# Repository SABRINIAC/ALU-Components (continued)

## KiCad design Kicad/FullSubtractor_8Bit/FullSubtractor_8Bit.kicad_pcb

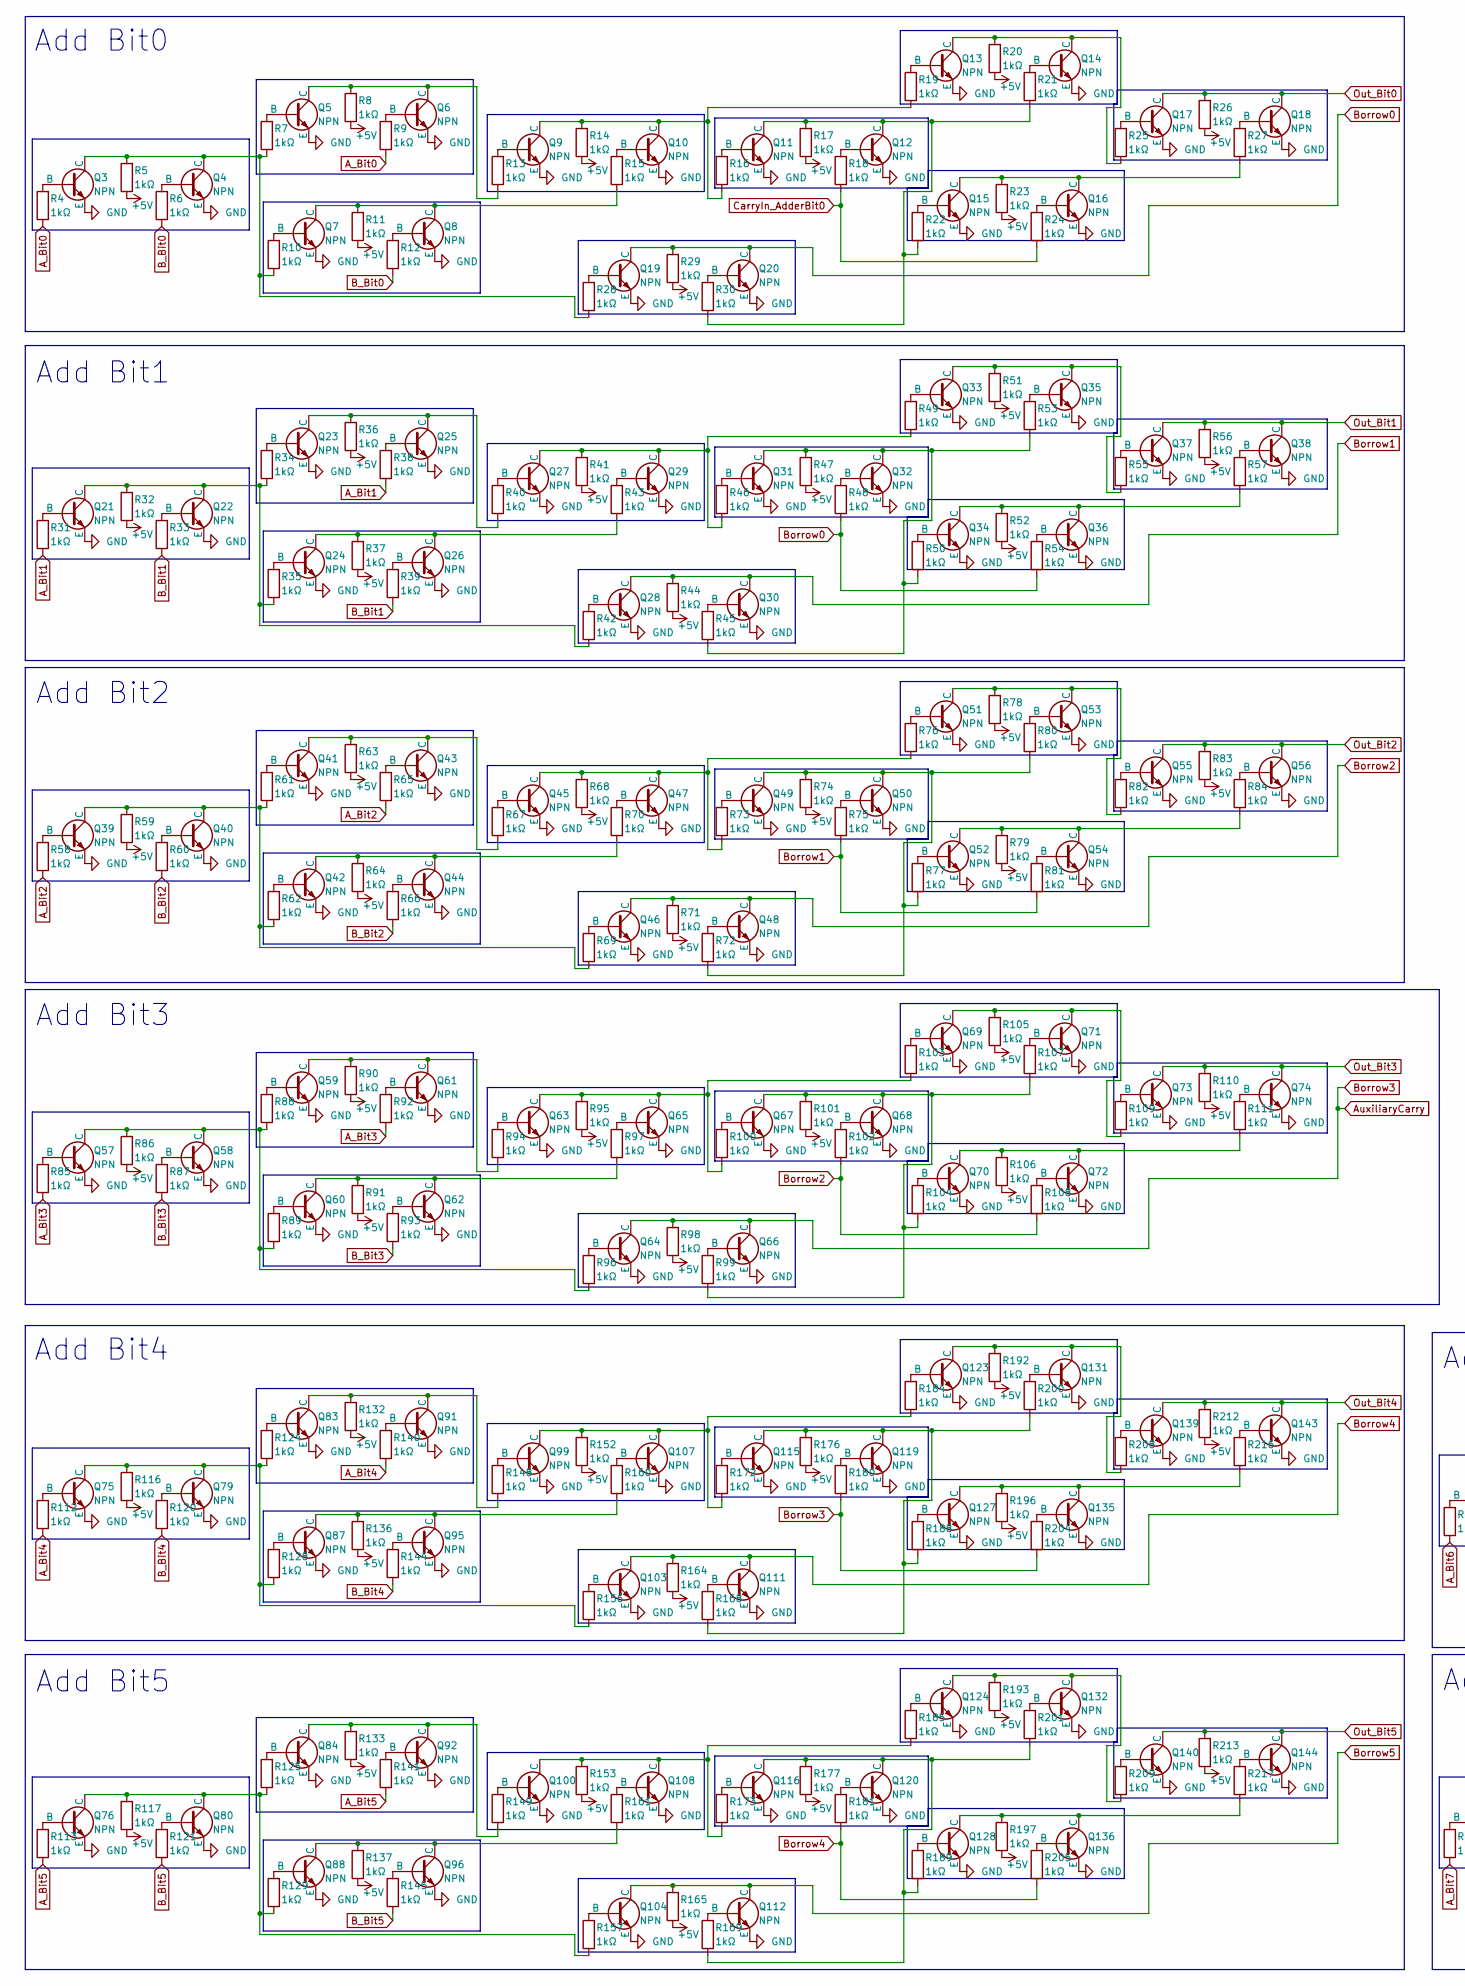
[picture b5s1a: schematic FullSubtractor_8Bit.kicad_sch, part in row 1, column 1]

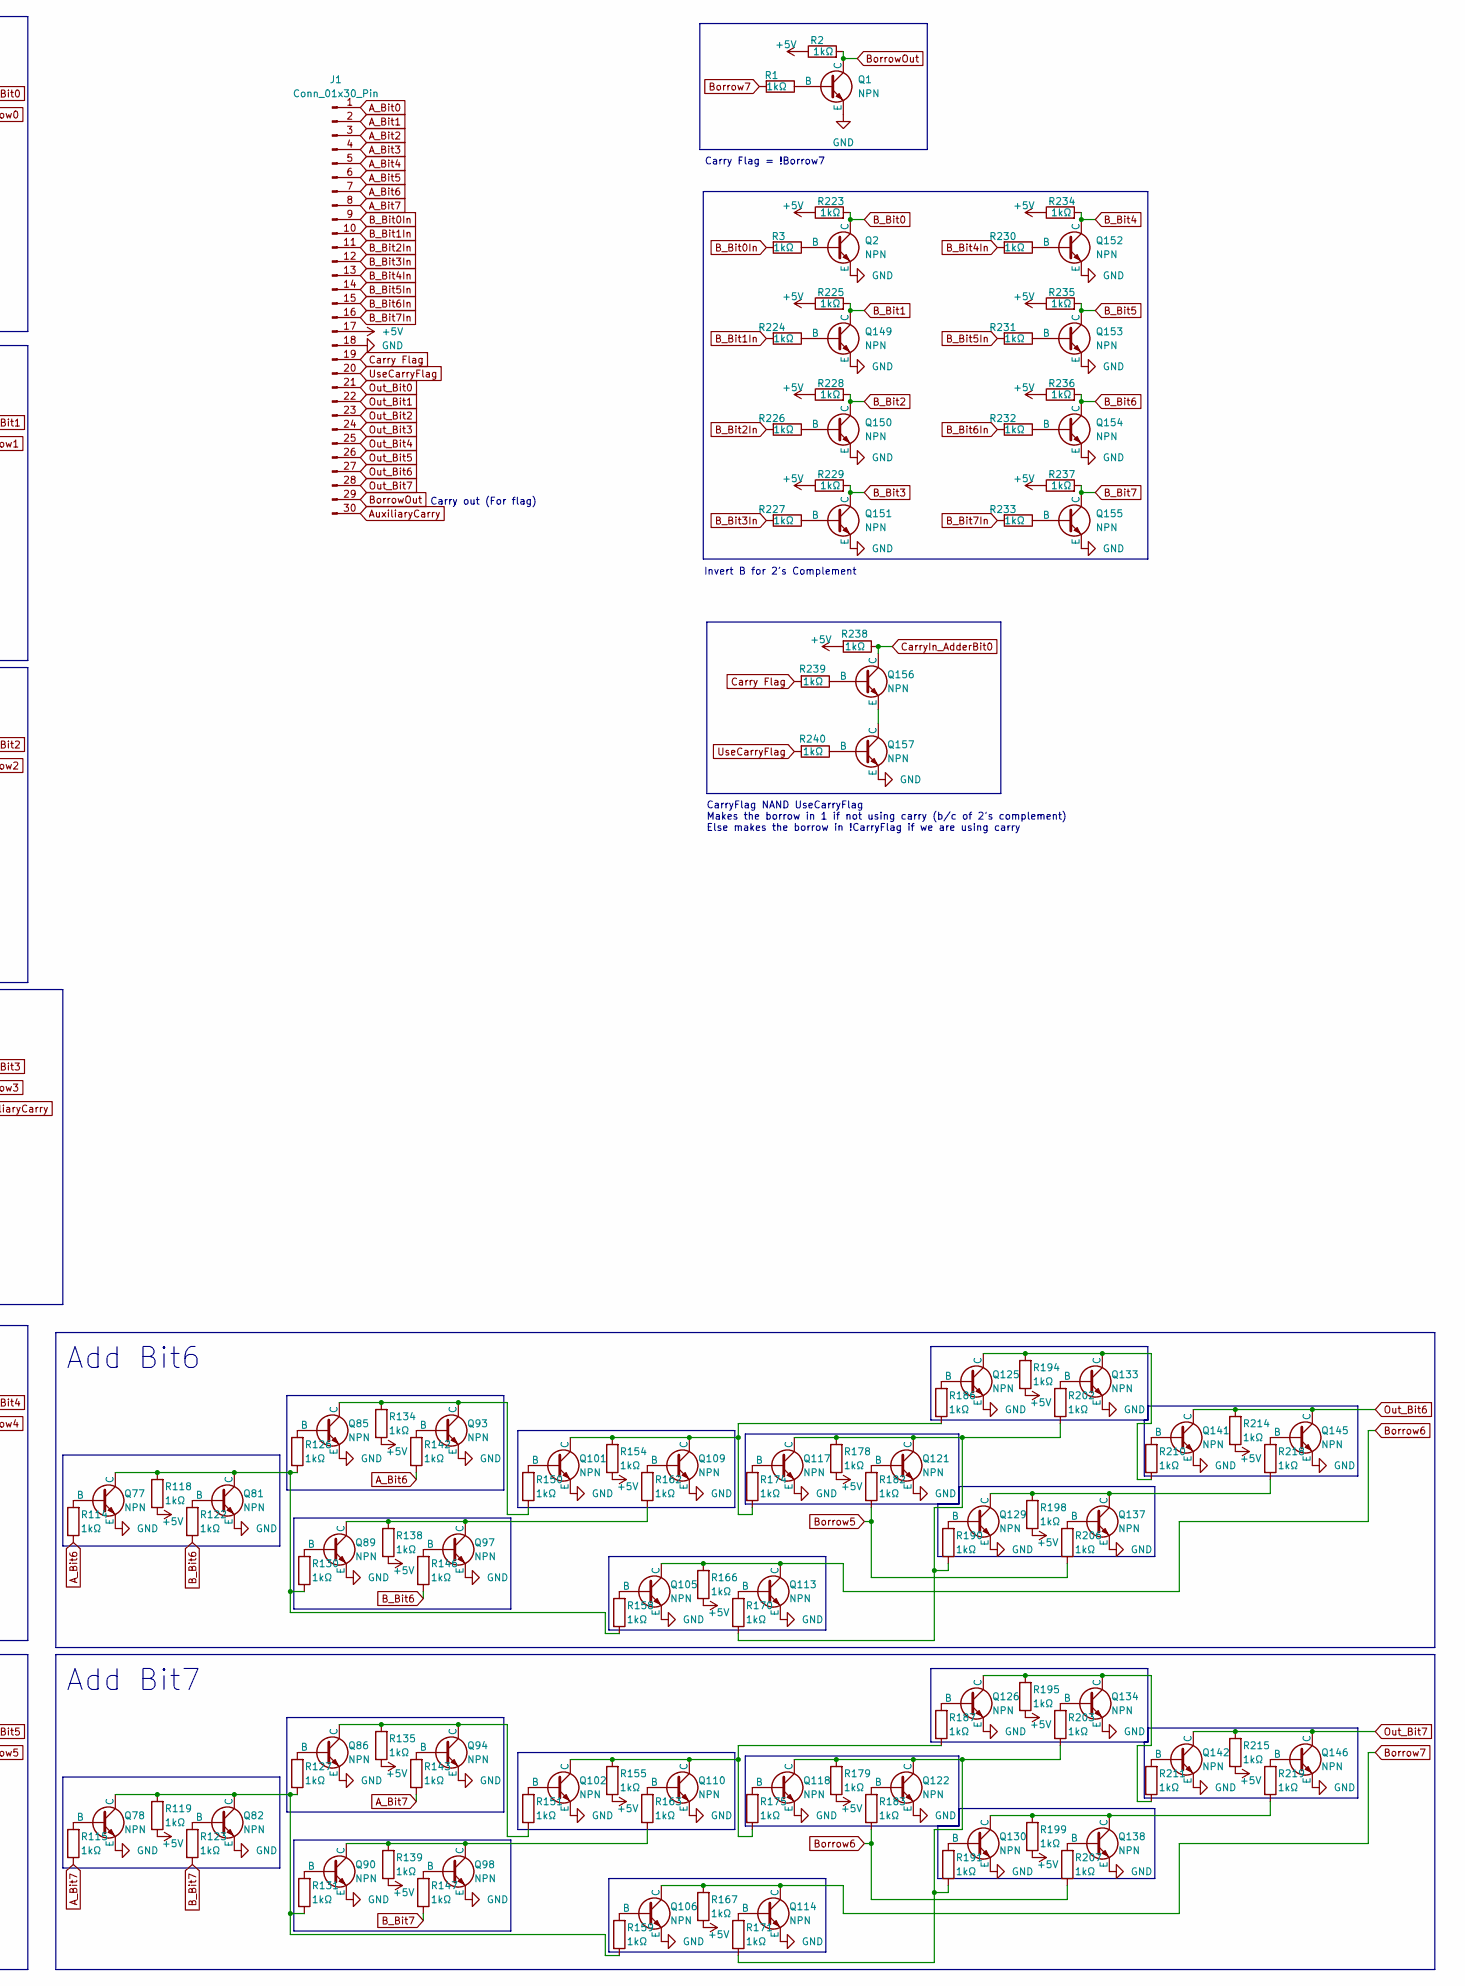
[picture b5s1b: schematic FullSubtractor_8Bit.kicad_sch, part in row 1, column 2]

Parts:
J1: Conn_01x30_Pin; PinHeader_1x30_P2.54mm_Horizontal
Q1, Q2, Q3, Q4, Q5, Q6, Q7, Q8, Q9, Q10, Q11, Q12, Q13, Q14, Q15, Q16, Q17, Q18, Q19, Q20, Q21, Q22, Q23, Q24, Q25, Q26, Q27, Q28, Q29, Q30, Q31, Q32, Q33, Q34, Q35, Q36, Q37, Q38, Q39, Q40, Q41, Q42, Q43, Q44, Q45, Q46, Q47, Q48, Q49, Q50, Q51, Q52, Q53, Q54, Q55, Q56, Q57, Q58, Q59, Q60, Q61, Q62, Q63, Q64, Q65, Q66, Q67, Q68, Q69, Q70, Q71, Q72, Q73, Q74, Q75, Q76, Q77, Q78, Q79, Q80, Q81, Q82, Q83, Q84, Q85, Q86, Q87, Q88, Q89, Q90, Q91, Q92, Q93, Q94, Q95, Q96, Q97, Q98, Q99, Q100, Q101, Q102, Q103, Q104, Q105, Q106, Q107, Q108, Q109, Q110, Q111, Q112, Q113, Q114, Q115, Q116, Q117, Q118, Q119, Q120, Q121, Q122, Q123, Q124, Q125, Q126, Q127, Q128, Q129, Q130, Q131, Q132, Q133, Q134, Q135, Q136, Q137, Q138, Q139, Q140, Q141, Q142, Q143, Q144, Q145, Q146, Q149, Q150, Q151, Q152, Q153, Q154, Q155, Q156, Q157: NPN; TO-92
R1, R2, R3, R4, R5, R6, R7, R8, R9, R10, R11, R12, R13, R14, R15, R16, R17, R18, R19, R20, R21, R22, R23, R24, R25, R26, R27, R28, R29, R30, R31, R32, R33, R34, R35, R36, R37, R38, R39, R40, R41, R42, R43, R44, R45, R46, R47, R48, R49, R50, R51, R52, R53, R54, R55, R56, R57, R58, R59, R60, R61, R62, R63, R64, R65, R66, R67, R68, R69, R70, R71, R72, R73, R74, R75, R76, R77, R78, R79, R80, R81, R82, R83, R84, R85, R86, R87, R88, R89, R90, R91, R92, R93, R94, R95, R96, R97, R98, R99, R100, R101, R102, R103, R104, R105, R106, R107, R108, R109, R110, R111, R112, R113, R114, R115, R116, R117, R118, R119, R120, R121, R122, R123, R124, R125, R126, R127, R128, R129, R130, R131, R132, R133, R134, R135, R136, R137, R138, R139, R140, R141, R142, R143, R144, R145, R146, R147, R148, R149, R150, R151, R152, R153, R154, R155, R156, R157, R158, R159, R160, R161, R162, R163, R164, R165, R166, R167, R168, R169, R170, R171, R172, R173, R174, R175, R176, R177, R178, R179, R180, R181, R182, R183, R184, R185, R186, R187, R188, R189, R190, R191, R192, R193, R194, R195, R196, R197, R198, R199, R200, R201, R202, R203, R204, R205, R206, R207, R208, R209, R210, R211, R212, R213, R214, R215, R216, R217, R218, R219, R223, R224, R225, R226, R227, R228, R229, R230, R231, R232, R233, R234, R235, R236, R237, R238, R239, R240: 1kΩ; R_0603_1608Metric

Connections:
+5V: J1.17, R2.1, R5.1, R8.1, R11.1, R14.1, R17.1, R20.1, R23.1, R26.1, R29.1, R32.1, R36.1, R37.1, R41.1, R44.1, R47.1, R51.1, R52.1, R56.1, R59.1, R63.1, R64.1, R68.1, R71.1, R74.1, R78.1, R79.1, R83.1, R86.1, R90.1, R91.1, R95.1, R98.1, R101.1, R105.1, R106.1, R110.1, R116.1, R117.1, R118.1, R119.1, R132.1, R133.1, R134.1, R135.1, R136.1, R137.1, R138.1, R139.1, R152.1, R153.1, R154.1, R155.1, R164.1, R165.1, R166.1, R167.1, R176.1, R177.1, R178.1, R179.1, R192.1, R193.1, R194.1, R195.1, R196.1, R197.1, R198.1, R199.1, R212.1, R213.1, R214.1, R215.1, R223.1, R225.1, R228.1, R229.1, R234.1, R235.1, R236.1, R237.1, R238.2
A_Bit0: J1.1, R4.1, R9.1
A_Bit1: J1.2, R31.1, R38.1
A_Bit2: J1.3, R58.1, R65.1
A_Bit3: J1.4, R85.1, R92.1
A_Bit4: J1.5, R112.1, R140.1
A_Bit5: J1.6, R113.1, R141.1
A_Bit6: J1.7, R114.1, R142.1
A_Bit7: J1.8, R115.1, R143.1
AuxiliaryCarry: J1.30, Q64.1 (C), Q66.1 (C), R98.2, R180.1, R204.1
B_Bit0: Q2.1 (C), R6.1, R12.1, R223.2
B_Bit0In: J1.9, R3.2
B_Bit1: Q149.1 (C), R33.1, R39.1, R225.2
B_Bit1In: J1.10, R224.2
B_Bit2: Q150.1 (C), R60.1, R66.1, R228.2
B_Bit2In: J1.11, R226.2
B_Bit3: Q151.1 (C), R87.1, R93.1, R229.2
B_Bit3In: J1.12, R227.2
B_Bit4: Q152.1 (C), R120.1, R144.1, R234.2
B_Bit4In: J1.13, R230.2
B_Bit5: Q153.1 (C), R121.1, R145.1, R235.2
B_Bit5In: J1.14, R231.2
B_Bit6: Q154.1 (C), R122.1, R146.1, R236.2
B_Bit6In: J1.15, R232.2
B_Bit7: Q155.1 (C), R123.1, R147.1, R237.2
B_Bit7In: J1.16, R233.2
Borrow0: Q19.1 (C), Q20.1 (C), R29.2, R48.1, R54.1
Borrow1: Q28.1 (C), Q30.1 (C), R44.2, R75.1, R81.1
Borrow2: Q46.1 (C), Q48.1 (C), R71.2, R102.1, R108.1
Borrow4: Q103.1 (C), Q111.1 (C), R164.2, R181.1, R205.1
Borrow5: Q104.1 (C), Q112.1 (C), R165.2, R182.1, R206.1
Borrow6: Q105.1 (C), Q113.1 (C), R166.2, R183.1, R207.1
Borrow7: Q106.1 (C), Q114.1 (C), R1.2, R167.2
BorrowOut: J1.29, Q1.1 (C), R2.2
Carry Flag: J1.19, R239.2
CarryIn_AdderBit0: Q156.1 (C), R18.1, R24.1, R238.1
GND: J1.18, Q1.3 (E), Q2.3 (E), Q3.3 (E), Q4.3 (E), Q5.3 (E), Q6.3 (E), Q7.3 (E), Q8.3 (E), Q9.3 (E), Q10.3 (E), Q11.3 (E), Q12.3 (E), Q13.3 (E), Q14.3 (E), Q15.3 (E), Q16.3 (E), Q17.3 (E), Q18.3 (E), Q19.3 (E), Q20.3 (E), Q21.3 (E), Q22.3 (E), Q23.3 (E), Q24.3 (E), Q25.3 (E), Q26.3 (E), Q27.3 (E), Q28.3 (E), Q29.3 (E), Q30.3 (E), Q31.3 (E), Q32.3 (E), Q33.3 (E), Q34.3 (E), Q35.3 (E), Q36.3 (E), Q37.3 (E), Q38.3 (E), Q39.3 (E), Q40.3 (E), Q41.3 (E), Q42.3 (E), Q43.3 (E), Q44.3 (E), Q45.3 (E), Q46.3 (E), Q47.3 (E), Q48.3 (E), Q49.3 (E), Q50.3 (E), Q51.3 (E), Q52.3 (E), Q53.3 (E), Q54.3 (E), Q55.3 (E), Q56.3 (E), Q57.3 (E), Q58.3 (E), Q59.3 (E), Q60.3 (E), Q61.3 (E), Q62.3 (E), Q63.3 (E), Q64.3 (E), Q65.3 (E), Q66.3 (E), Q67.3 (E), Q68.3 (E), Q69.3 (E), Q70.3 (E), Q71.3 (E), Q72.3 (E), Q73.3 (E), Q74.3 (E), Q75.3 (E), Q76.3 (E), Q77.3 (E), Q78.3 (E), Q79.3 (E), Q80.3 (E), Q81.3 (E), Q82.3 (E), Q83.3 (E), Q84.3 (E), Q85.3 (E), Q86.3 (E), Q87.3 (E), Q88.3 (E), Q89.3 (E), Q90.3 (E), Q91.3 (E), Q92.3 (E), Q93.3 (E), Q94.3 (E), Q95.3 (E), Q96.3 (E), Q97.3 (E), Q98.3 (E), Q99.3 (E), Q100.3 (E), Q101.3 (E), Q102.3 (E), Q103.3 (E), Q104.3 (E), Q105.3 (E), Q106.3 (E), Q107.3 (E), Q108.3 (E), Q109.3 (E), Q110.3 (E), Q111.3 (E), Q112.3 (E), Q113.3 (E), Q114.3 (E), Q115.3 (E), Q116.3 (E), Q117.3 (E), Q118.3 (E), Q119.3 (E), Q120.3 (E), Q121.3 (E), Q122.3 (E), Q123.3 (E), Q124.3 (E), Q125.3 (E), Q126.3 (E), Q127.3 (E), Q128.3 (E), Q129.3 (E), Q130.3 (E), Q131.3 (E), Q132.3 (E), Q133.3 (E), Q134.3 (E), Q135.3 (E), Q136.3 (E), Q137.3 (E), Q138.3 (E), Q139.3 (E), Q140.3 (E), Q141.3 (E), Q142.3 (E), Q143.3 (E), Q144.3 (E), Q145.3 (E), Q146.3 (E), Q149.3 (E), Q150.3 (E), Q151.3 (E), Q152.3 (E), Q153.3 (E), Q154.3 (E), Q155.3 (E), Q157.3 (E)
unnamed: Q1.2 (B), R1.1
unnamed: Q2.2 (B), R3.1
unnamed: Q3.2 (B), R4.2
unnamed: Q3.1 (C), Q4.1 (C), R5.2, R7.1, R10.1, R28.1
unnamed: Q4.2 (B), R6.2
unnamed: Q5.2 (B), R7.2
unnamed: Q5.1 (C), Q6.1 (C), R8.2, R13.1
unnamed: Q6.2 (B), R9.2
unnamed: Q7.2 (B), R10.2
unnamed: Q7.1 (C), Q8.1 (C), R11.2, R15.1
unnamed: Q8.2 (B), R12.2
unnamed: Q9.2 (B), R13.2
unnamed: Q10.2 (B), R15.2
unnamed: Q9.1 (C), Q10.1 (C), R14.2, R16.1, R19.1
unnamed: Q11.2 (B), R16.2
unnamed: Q11.1 (C), Q12.1 (C), R17.2, R21.1, R22.1, R30.1
unnamed: Q12.2 (B), R18.2
unnamed: Q13.2 (B), R19.2
unnamed: Q13.1 (C), Q14.1 (C), R20.2, R25.1
unnamed: Q14.2 (B), R21.2
unnamed: Q15.2 (B), R22.2
unnamed: Q15.1 (C), Q16.1 (C), R23.2, R27.1
unnamed: Q16.2 (B), R24.2
unnamed: Q17.2 (B), R25.2
unnamed: Q18.2 (B), R27.2
unnamed: Q19.2 (B), R28.2
unnamed: Q20.2 (B), R30.2
unnamed: Q21.2 (B), R31.2
unnamed: Q21.1 (C), Q22.1 (C), R32.2, R34.1, R35.1, R42.1
unnamed: Q22.2 (B), R33.2
unnamed: Q23.2 (B), R34.2
unnamed: Q23.1 (C), Q25.1 (C), R36.2, R40.1
unnamed: Q24.2 (B), R35.2
unnamed: Q24.1 (C), Q26.1 (C), R37.2, R43.1
unnamed: Q25.2 (B), R38.2
unnamed: Q26.2 (B), R39.2
unnamed: Q27.2 (B), R40.2
unnamed: Q27.1 (C), Q29.1 (C), R41.2, R46.1, R49.1
unnamed: Q28.2 (B), R42.2
unnamed: Q29.2 (B), R43.2
unnamed: Q30.2 (B), R45.2
unnamed: Q31.2 (B), R46.2
unnamed: Q31.1 (C), Q32.1 (C), R45.1, R47.2, R50.1, R53.1
unnamed: Q32.2 (B), R48.2
unnamed: Q33.2 (B), R49.2
unnamed: Q33.1 (C), Q35.1 (C), R51.2, R55.1
unnamed: Q34.2 (B), R50.2
unnamed: Q34.1 (C), Q36.1 (C), R52.2, R57.1
unnamed: Q35.2 (B), R53.2
unnamed: Q36.2 (B), R54.2
unnamed: Q37.2 (B), R55.2
unnamed: Q38.2 (B), R57.2
unnamed: Q39.2 (B), R58.2
unnamed: Q39.1 (C), Q40.1 (C), R59.2, R61.1, R62.1, R69.1
unnamed: Q40.2 (B), R60.2
unnamed: Q41.2 (B), R61.2
unnamed: Q41.1 (C), Q43.1 (C), R63.2, R67.1
unnamed: Q42.2 (B), R62.2
unnamed: Q42.1 (C), Q44.1 (C), R64.2, R70.1
unnamed: Q43.2 (B), R65.2
unnamed: Q44.2 (B), R66.2
unnamed: Q45.2 (B), R67.2
unnamed: Q45.1 (C), Q47.1 (C), R68.2, R73.1, R76.1
unnamed: Q46.2 (B), R69.2
unnamed: Q47.2 (B), R70.2
unnamed: Q48.2 (B), R72.2
unnamed: Q49.2 (B), R73.2
unnamed: Q49.1 (C), Q50.1 (C), R72.1, R74.2, R77.1, R80.1
unnamed: Q50.2 (B), R75.2
unnamed: Q51.2 (B), R76.2
unnamed: Q51.1 (C), Q53.1 (C), R78.2, R82.1
unnamed: Q52.2 (B), R77.2
unnamed: Q52.1 (C), Q54.1 (C), R79.2, R84.1
unnamed: Q53.2 (B), R80.2
unnamed: Q54.2 (B), R81.2
unnamed: Q55.2 (B), R82.2
unnamed: Q56.2 (B), R84.2
unnamed: Q57.2 (B), R85.2
unnamed: Q57.1 (C), Q58.1 (C), R86.2, R88.1, R89.1, R96.1
unnamed: Q58.2 (B), R87.2
unnamed: Q59.2 (B), R88.2
unnamed: Q59.1 (C), Q61.1 (C), R90.2, R94.1
unnamed: Q60.2 (B), R89.2
unnamed: Q60.1 (C), Q62.1 (C), R91.2, R97.1
unnamed: Q61.2 (B), R92.2
unnamed: Q62.2 (B), R93.2
unnamed: Q63.2 (B), R94.2
unnamed: Q63.1 (C), Q65.1 (C), R95.2, R100.1, R103.1
unnamed: Q64.2 (B), R96.2
unnamed: Q65.2 (B), R97.2
unnamed: Q66.2 (B), R99.2
unnamed: Q67.2 (B), R100.2
unnamed: Q67.1 (C), Q68.1 (C), R99.1, R101.2, R104.1, R107.1
unnamed: Q68.2 (B), R102.2
unnamed: Q69.2 (B), R103.2
unnamed: Q69.1 (C), Q71.1 (C), R105.2, R109.1
unnamed: Q70.2 (B), R104.2
unnamed: Q70.1 (C), Q72.1 (C), R106.2, R111.1
unnamed: Q71.2 (B), R107.2
unnamed: Q72.2 (B), R108.2
unnamed: Q73.2 (B), R109.2
unnamed: Q74.2 (B), R111.2
unnamed: Q75.2 (B), R112.2
unnamed: Q75.1 (C), Q79.1 (C), R116.2, R124.1, R128.1, R156.1
unnamed: Q76.2 (B), R113.2
unnamed: Q76.1 (C), Q80.1 (C), R117.2, R125.1, R129.1, R157.1
unnamed: Q77.2 (B), R114.2
unnamed: Q77.1 (C), Q81.1 (C), R118.2, R126.1, R130.1, R158.1
unnamed: Q78.2 (B), R115.2
unnamed: Q78.1 (C), Q82.1 (C), R119.2, R127.1, R131.1, R159.1
unnamed: Q79.2 (B), R120.2
unnamed: Q80.2 (B), R121.2
unnamed: Q81.2 (B), R122.2
unnamed: Q82.2 (B), R123.2
unnamed: Q83.2 (B), R124.2
unnamed: Q83.1 (C), Q91.1 (C), R132.2, R148.1
unnamed: Q84.2 (B), R125.2
unnamed: Q84.1 (C), Q92.1 (C), R133.2, R149.1
unnamed: Q85.2 (B), R126.2
unnamed: Q85.1 (C), Q93.1 (C), R134.2, R150.1
unnamed: Q86.2 (B), R127.2
unnamed: Q86.1 (C), Q94.1 (C), R135.2, R151.1
unnamed: Q87.2 (B), R128.2
unnamed: Q87.1 (C), Q95.1 (C), R136.2, R160.1
unnamed: Q88.2 (B), R129.2
unnamed: Q88.1 (C), Q96.1 (C), R137.2, R161.1
unnamed: Q89.2 (B), R130.2
unnamed: Q89.1 (C), Q97.1 (C), R138.2, R162.1
unnamed: Q90.2 (B), R131.2
unnamed: Q90.1 (C), Q98.1 (C), R139.2, R163.1
unnamed: Q91.2 (B), R140.2
unnamed: Q92.2 (B), R141.2
unnamed: Q93.2 (B), R142.2
unnamed: Q94.2 (B), R143.2
unnamed: Q95.2 (B), R144.2
unnamed: Q96.2 (B), R145.2
unnamed: Q97.2 (B), R146.2
unnamed: Q98.2 (B), R147.2
unnamed: Q99.2 (B), R148.2
unnamed: Q100.2 (B), R149.2
unnamed: Q100.1 (C), Q108.1 (C), R153.2, R173.1, R185.1
unnamed: Q101.2 (B), R150.2
unnamed: Q101.1 (C), Q109.1 (C), R154.2, R174.1, R186.1
unnamed: Q102.2 (B), R151.2
unnamed: Q102.1 (C), Q110.1 (C), R155.2, R175.1, R187.1
unnamed: Q103.2 (B), R156.2
unnamed: Q104.2 (B), R157.2
unnamed: Q105.2 (B), R158.2
unnamed: Q106.2 (B), R159.2
unnamed: Q107.2 (B), R160.2
unnamed: Q99.1 (C), Q107.1 (C), R152.2, R172.1, R184.1
unnamed: Q108.2 (B), R161.2
unnamed: Q109.2 (B), R162.2
unnamed: Q110.2 (B), R163.2
unnamed: Q111.2 (B), R168.2
unnamed: Q112.2 (B), R169.2
unnamed: Q113.2 (B), R170.2
unnamed: Q114.2 (B), R171.2
unnamed: Q115.2 (B), R172.2
unnamed: Q115.1 (C), Q119.1 (C), R168.1, R176.2, R188.1, R200.1
unnamed: Q116.2 (B), R173.2
unnamed: Q116.1 (C), Q120.1 (C), R169.1, R177.2, R189.1, R201.1
unnamed: Q117.2 (B), R174.2
unnamed: Q117.1 (C), Q121.1 (C), R170.1, R178.2, R190.1, R202.1
unnamed: Q118.2 (B), R175.2
unnamed: Q118.1 (C), Q122.1 (C), R171.1, R179.2, R191.1, R203.1
unnamed: Q119.2 (B), R180.2
unnamed: Q120.2 (B), R181.2
unnamed: Q121.2 (B), R182.2
unnamed: Q122.2 (B), R183.2
unnamed: Q123.2 (B), R184.2
unnamed: Q123.1 (C), Q131.1 (C), R192.2, R208.1
unnamed: Q124.2 (B), R185.2
unnamed: Q124.1 (C), Q132.1 (C), R193.2, R209.1
unnamed: Q125.2 (B), R186.2
unnamed: Q125.1 (C), Q133.1 (C), R194.2, R210.1
unnamed: Q126.2 (B), R187.2
unnamed: Q126.1 (C), Q134.1 (C), R195.2, R211.1
unnamed: Q127.2 (B), R188.2
unnamed: Q127.1 (C), Q135.1 (C), R196.2, R216.1
unnamed: Q128.2 (B), R189.2
unnamed: Q128.1 (C), Q136.1 (C), R197.2, R217.1
unnamed: Q129.2 (B), R190.2
unnamed: Q129.1 (C), Q137.1 (C), R198.2, R218.1
unnamed: Q130.2 (B), R191.2
unnamed: Q130.1 (C), Q138.1 (C), R199.2, R219.1
unnamed: Q131.2 (B), R200.2
unnamed: Q132.2 (B), R201.2
unnamed: Q133.2 (B), R202.2
unnamed: Q134.2 (B), R203.2
unnamed: Q135.2 (B), R204.2
unnamed: Q136.2 (B), R205.2
unnamed: Q137.2 (B), R206.2
unnamed: Q138.2 (B), R207.2
unnamed: Q139.2 (B), R208.2
unnamed: Q140.2 (B), R209.2
unnamed: Q141.2 (B), R210.2
unnamed: Q142.2 (B), R211.2
unnamed: Q143.2 (B), R216.2
unnamed: Q144.2 (B), R217.2
unnamed: Q145.2 (B), R218.2
unnamed: Q146.2 (B), R219.2
unnamed: Q149.2 (B), R224.1
unnamed: Q150.2 (B), R226.1
unnamed: Q151.2 (B), R227.1
unnamed: Q152.2 (B), R230.1
unnamed: Q153.2 (B), R231.1
unnamed: Q154.2 (B), R232.1
unnamed: Q155.2 (B), R233.1
unnamed: Q156.2 (B), R239.1
unnamed: Q156.3 (E), Q157.1 (C)
unnamed: Q157.2 (B), R240.1
Out_Bit0: J1.21, Q17.1 (C), Q18.1 (C), R26.2
Out_Bit1: J1.22, Q37.1 (C), Q38.1 (C), R56.2
Out_Bit2: J1.23, Q55.1 (C), Q56.1 (C), R83.2
Out_Bit3: J1.24, Q73.1 (C), Q74.1 (C), R110.2
Out_Bit4: J1.25, Q139.1 (C), Q143.1 (C), R212.2
Out_Bit5: J1.26, Q140.1 (C), Q144.1 (C), R213.2
Out_Bit6: J1.27, Q141.1 (C), Q145.1 (C), R214.2
Out_Bit7: J1.28, Q142.1 (C), Q146.1 (C), R215.2
UseCarryFlag: J1.20, R240.2

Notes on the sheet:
Add Bit2
Add Bit1
Add Bit5
Carry Flag = !Borrow7
Add Bit0
Add Bit3
Add Bit4
Add Bit6
Carry out (For flag)
CarryFlag NAND UseCarryFlag Makes the borrow in 1 if not using carry (b/c of 2's complement) Else makes the borrow in !CarryFlag if we are using carry
Add Bit7
Invert B for 2's Complement

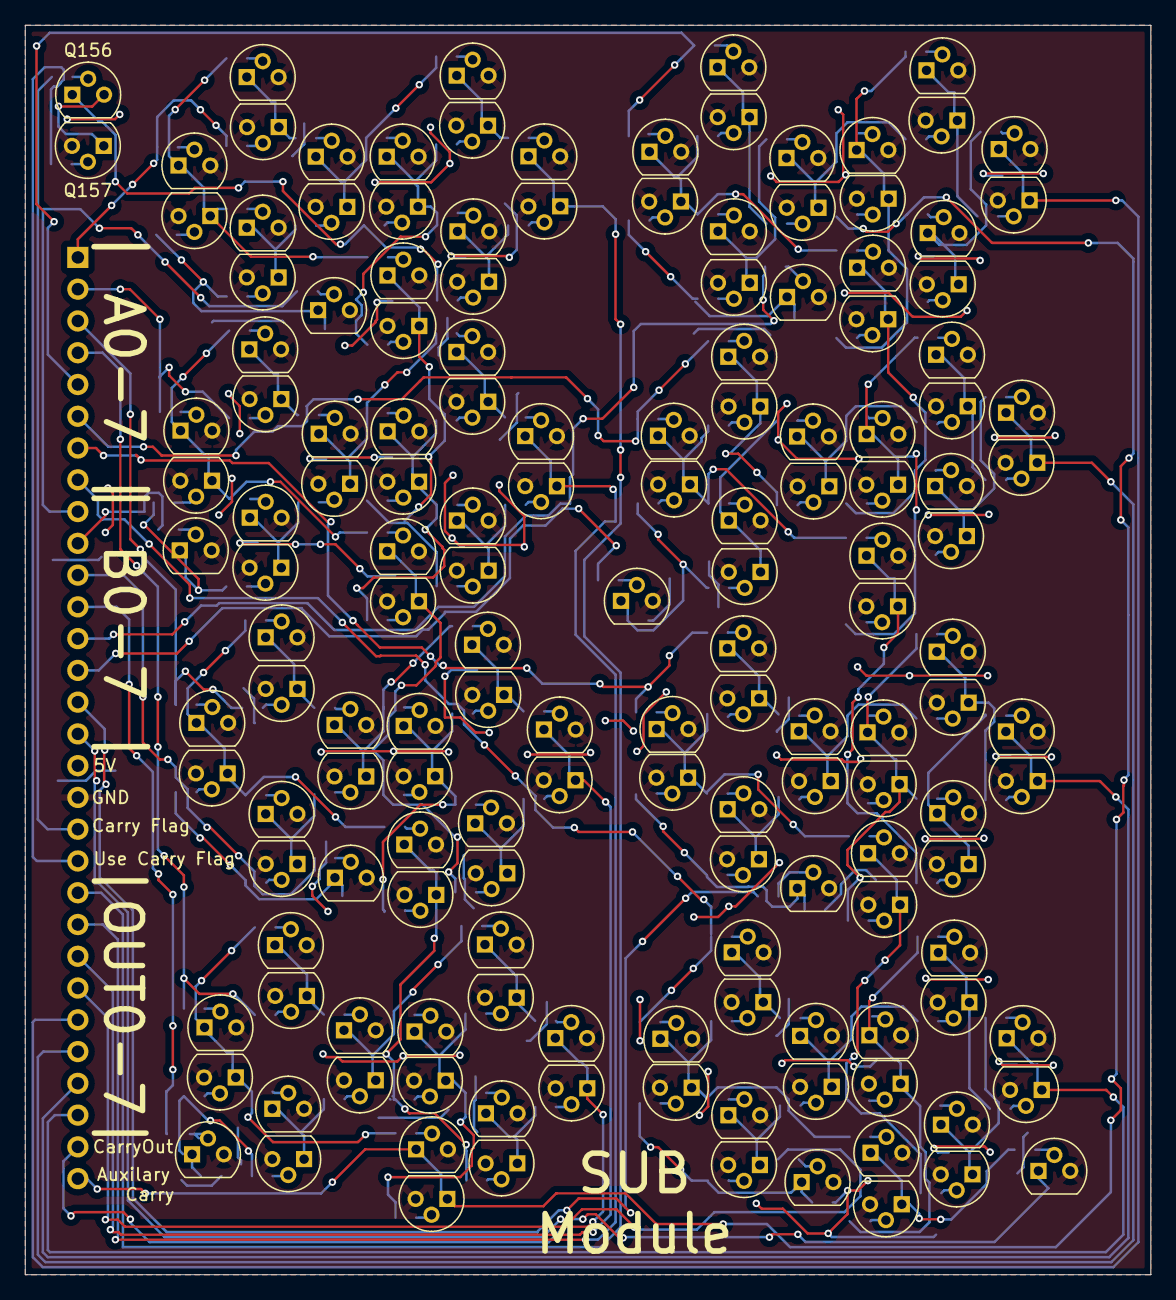
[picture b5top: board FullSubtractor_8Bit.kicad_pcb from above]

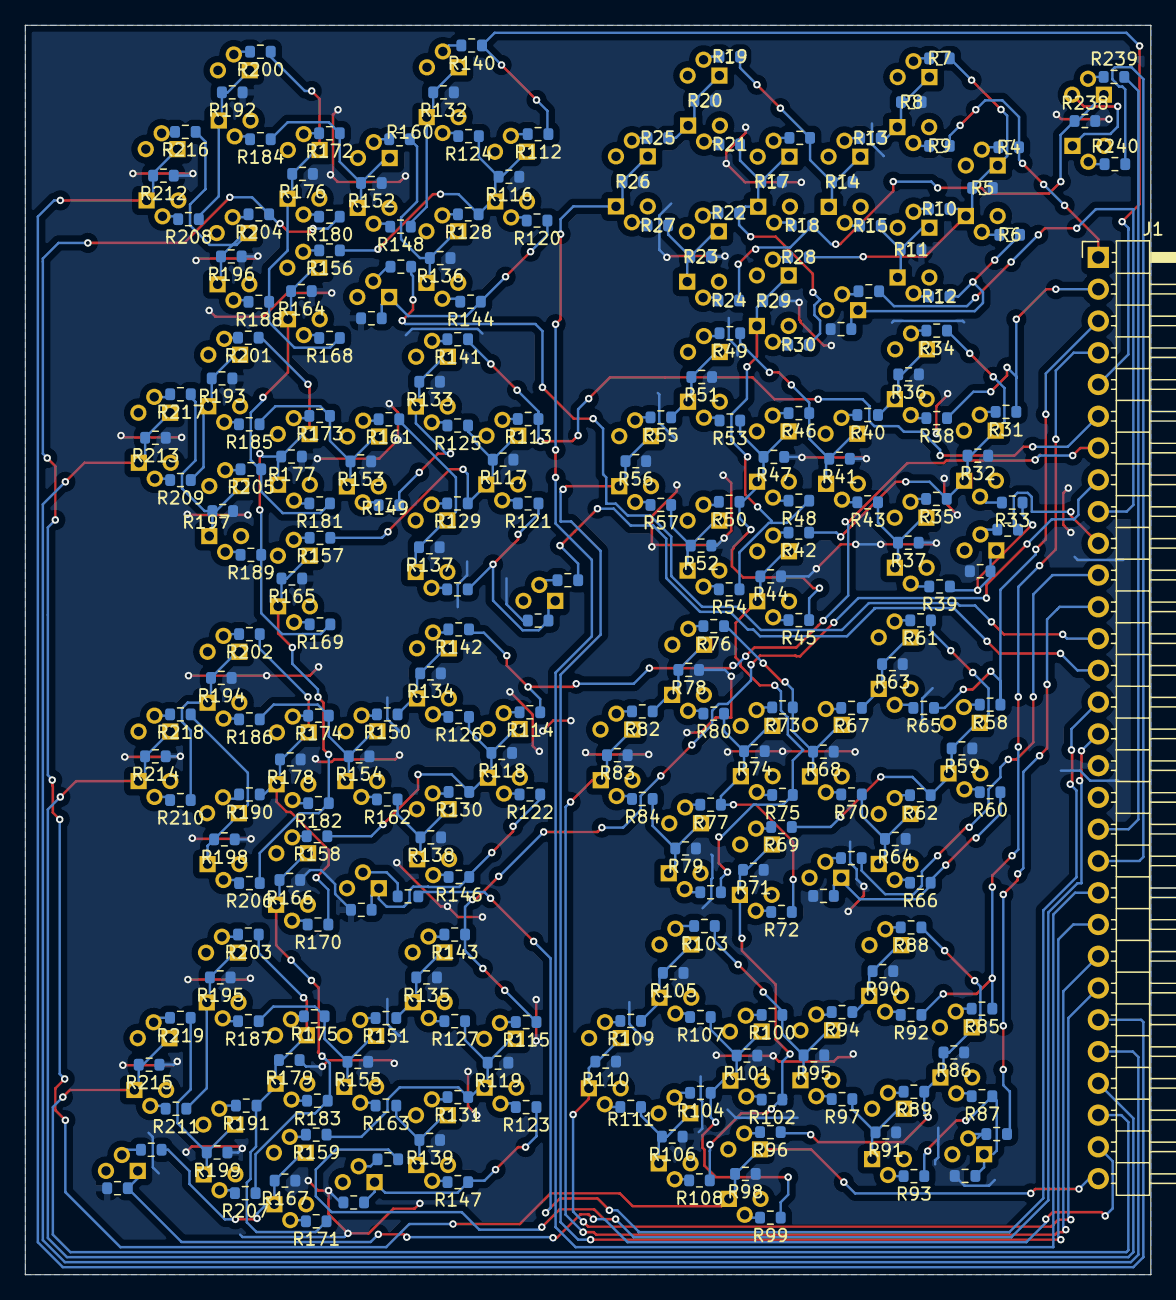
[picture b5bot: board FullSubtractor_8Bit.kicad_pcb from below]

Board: 2 copper layers, 90.0 x 99.9 mm, 393 parts (238 on the bottom side), 258 nets.

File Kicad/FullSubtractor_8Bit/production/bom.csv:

Designator,Footprint,Quantity,Value,LCSC Part #
J1,PinHeader_1x30_P2.54mm_Horizontal,1,Conn_01x30_Pin,
"Q1, Q10, Q100, Q101, Q102, Q103, Q104, Q105, Q106, Q107, Q108, Q109, Q11, Q110, Q111, Q112, Q113, Q114, Q115, Q116, Q117, Q118, Q119, Q12, Q120, Q121, Q122, Q123, Q124, Q125, Q126, Q127, Q128, Q129, Q13, Q130, Q131, Q132, Q133, Q134, Q135, Q136, Q137, Q138, Q139, Q14, Q140, Q141, Q142, Q143, Q144, Q145, Q146, Q149, Q15, Q150, Q151, Q152, Q153, Q154, Q155, Q156, Q157, Q16, Q17, Q18, Q19, Q2, Q20, Q21, Q22, Q23, Q24, Q25, Q26, Q27, Q28, Q29, Q3, Q30, Q31, Q32, Q33, Q34, Q35, Q36, Q37, Q38, Q39, Q4, Q40, Q41, Q42, Q43, Q44, Q45, Q46, Q47, Q48, Q49, Q5, Q50, Q51, Q52, Q53, Q54, Q55, Q56, Q57, Q58, Q59, Q6, Q60, Q61, Q62, Q63, Q64, Q65, Q66, Q67, Q68, Q69, Q7, Q70, Q71, Q72, Q73, Q74, Q75, Q76, Q77, Q78, Q79, Q8, Q80, Q81, Q82, Q83, Q84, Q85, Q86, Q87, Q88, Q89, Q9, Q90, Q91, Q92, Q93, Q94, Q95, Q96, Q97, Q98, Q99",TO-92,155,NPN,
"R1, R10, R100, R101, R102, R103, R104, R105, R106, R107, R108, R109, R11, R110, R111, R112, R113, R114, R115, R116, R117, R118, R119, R12, R120, R121, R122, R123, R124, R125, R126, R127, R128, R129, R13, R130, R131, R132, R133, R134, R135, R136, R137, R138, R139, R14, R140, R141, R142, R143, R144, R145, R146, R147, R148, R149, R15, R150, R151, R152, R153, R154, R155, R156, R157, R158, R159, R16, R160, R161, R162, R163, R164, R165, R166, R167, R168, R169, R17, R170, R171, R172, R173, R174, R175, R176, R177, R178, R179, R18, R180, R181, R182, R183, R184, R185, R186, R187, R188, R189, R19, R190, R191, R192, R193, R194, R195, R196, R197, R198, R199, R2, R20, R200, R201, R202, R203, R204, R205, R206, R207, R208, R209, R21, R210, R211, R212, R213, R214, R215, R216, R217, R218, R219, R22, R223, R224, R225, R226, R227, R228, R229, R23, R230, R231, R232, R233, R234, R235, R236, R237, R238, R239, R24, R240, R25, R26, R27, R28, R29, R3, R30, R31, R32, R33, R34, R35, R36, R37, R38, R39, R4, R40, R41, R42, R43, R44, R45, R46, R47, R48, R49, R5, R50, R51, R52, R53, R54, R55, R56, R57, R58, R59, R6, R60, R61, R62, R63, R64, R65",0603,200,1kΩ,
"R66, R67, R68, R69, R7, R70, R71, R72, R73, R74, R75, R76, R77, R78, R79, R8, R80, R81, R82, R83, R84, R85, R86, R87, R88, R89, R9, R90, R91, R92, R93, R94, R95, R96, R97, R98, R99",0603,37,1kΩ,

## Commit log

2026-04-24 added what instructions will be included and their functions (minus DAA)
2026-04-24 Added line breaks in the README
2026-04-25 Created the ADD schematic and placed the components on the PCB, need to do routing still
2026-04-25 Did some routing!
2026-04-25 some kicad files locked removed
2026-04-26 Finished the ADD PCB
2026-04-26 Crossed out the adder b/c i have finished it
2026-04-26 Made a backup; removed all traces and put parts where they need to be. starting routing again
2026-04-27 Revert "Made a backup; removed all traces and put parts where they need to be. starting routing again"
    This reverts commit 2ef9f42e64e6a7f49d503f8bd060bf19175d52bc.
2026-04-27 Started making the subtractor
2026-04-27 8 Bit Subtractor Done!
2026-04-27 Crossed out SUB since it's done
2026-04-27 Bitwise AND Module fully complete
2026-04-27 Crossed out AND in the doc
2026-04-27 Bitwise OR is fully done; Plus i remembered to cross it out on the doc
2026-04-28 Finished the XOR module and added silk screens to OR, AND, and XOR
2026-04-28 added some modules to the doc
2026-04-28 DAA > 0x9 detector circuit in falstad
2026-04-28 Bitwise NOT module complete
2026-04-28 Finished Rotate Left and Rotate Right w/ through carry flag
2026-04-28 removed old things from the doc
2026-04-29 created the bom and updated the readme
2026-04-29 Generated fab files for all of the pcbs + a backup from kicad ig
2026-04-29 Added PCB Csot, and images to the readme
2026-04-29 Fixed formatting
2026-06-26 added built images
2026-06-26 fixed 1 image
2026-06-26 feat: added my test code for anyone trying to replicate this
